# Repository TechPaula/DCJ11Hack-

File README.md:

# DCJ11Hack+
DCJ11 Hack+ related boards, PAL code and example code
by Paula Maddox http://maddoxp.pro

This is my first github project, I've decided to share my DCJ11 based board. It's based heavily on the word done by Beent Hilpert http://madrona.ca/e/pdp11hack/ but I wanted to able to add and remove functionality via a back plane.

I've long admired this chip for no other reason than it looks so freekin' cool, I mean just look at it, it's gorgeous.

## The Boards
So far There is the main CPU board and also the RAM, ROM and text display board. You'll find the schematics and PCB files here and they were made in KiCAD. I've also included the PAL files for each of the PALs on the board (one on each board). Hopefully this will give you enough to get going.
The text displays are mounted on the opposite side to the RAM/ROM chips as I wanted to be able to see the text and also be able to turn it to see the DCJ11 chip (did I say how gorgeous this chip is?).

Now there's a 16x16 Dot Matrix display, it does have two levels of brightness (just two overlapping portions of 32 bytes of RAM), but the difference between dim and bright isn't very much.

I got my backplane from eBay here - https://www.ebay.co.uk/itm/284367015211 and the same seller also does backplanes with more slots.

When it powers up the chip jumps to it's "ODT" mode rather than running code, this was done to allow me to play around with thinngs and get an understanding of the chip. 
The default baud rate is 115200 and uses 8bits, 1 stop and no  parity. 

## Memory Map
My memory map is as follows and was updated on 07/04/2024;

### HEX
* 0x0000 - 0x7FFE = RAM  (32K)
* 0x6000 - 0x7FFE = Text Display (shadowed in RAM as it's WRITE only)
* 0x8000 - 0xBFFE = ROM  (16K)
* 0xC000 - 0xDFFE = Matrix display
* 0xE000 - 0xFFFE = Future

### OCTAL (has to end on a multiple of 2)
* 000 000 - 077 776 - RAM
* 060 000 - 060 020 - Text Display (repeated multiple times)
* 100 000 - 137 776 - ROM
* 140 000 - 157 776 - Matrix Display
* 160 000 - 177 776 - Future

## Code examples
The code examples are for a basic "Hello World!" which just writes characters to the display memory, there's also a more intelligent one. I've also included a "Knight Rider" (or Cylon if you prefer) bit of code and finally a terminal test code which spits "B" to the console (hit the halt switch to stop it).

You'll find the .asm files and the .oct files.

I use the pdp11 simulator found here https://programmer209.wordpress.com/2011/08/14/pdp-11-assembly-language-simulator/ to compile and test my code, there are others but this is a lot easier to copy and paste code into :)

There is also a pretty good guide to the PDP11 instruction set here - https://programmer209.wordpress.com/2011/08/03/the-pdp-11-assembly-language/

of note, this board **ONLY** supports 16bit wide read/writes, i.e. "word" only, if you use byte commands it will destroy one half of the memory, in the same way as the PDP11 Hack board does, this is less than ideal but it simplifies the circuitry needed a lot.

I user TeraTerm to upload the code, I use a 10mS character and line feed delay, just to give the CPU a chance to respond when it sees the "/".

## The future

Finally, I do this for a hobby and for fun, so I don't know when I will add more code or do the third board.

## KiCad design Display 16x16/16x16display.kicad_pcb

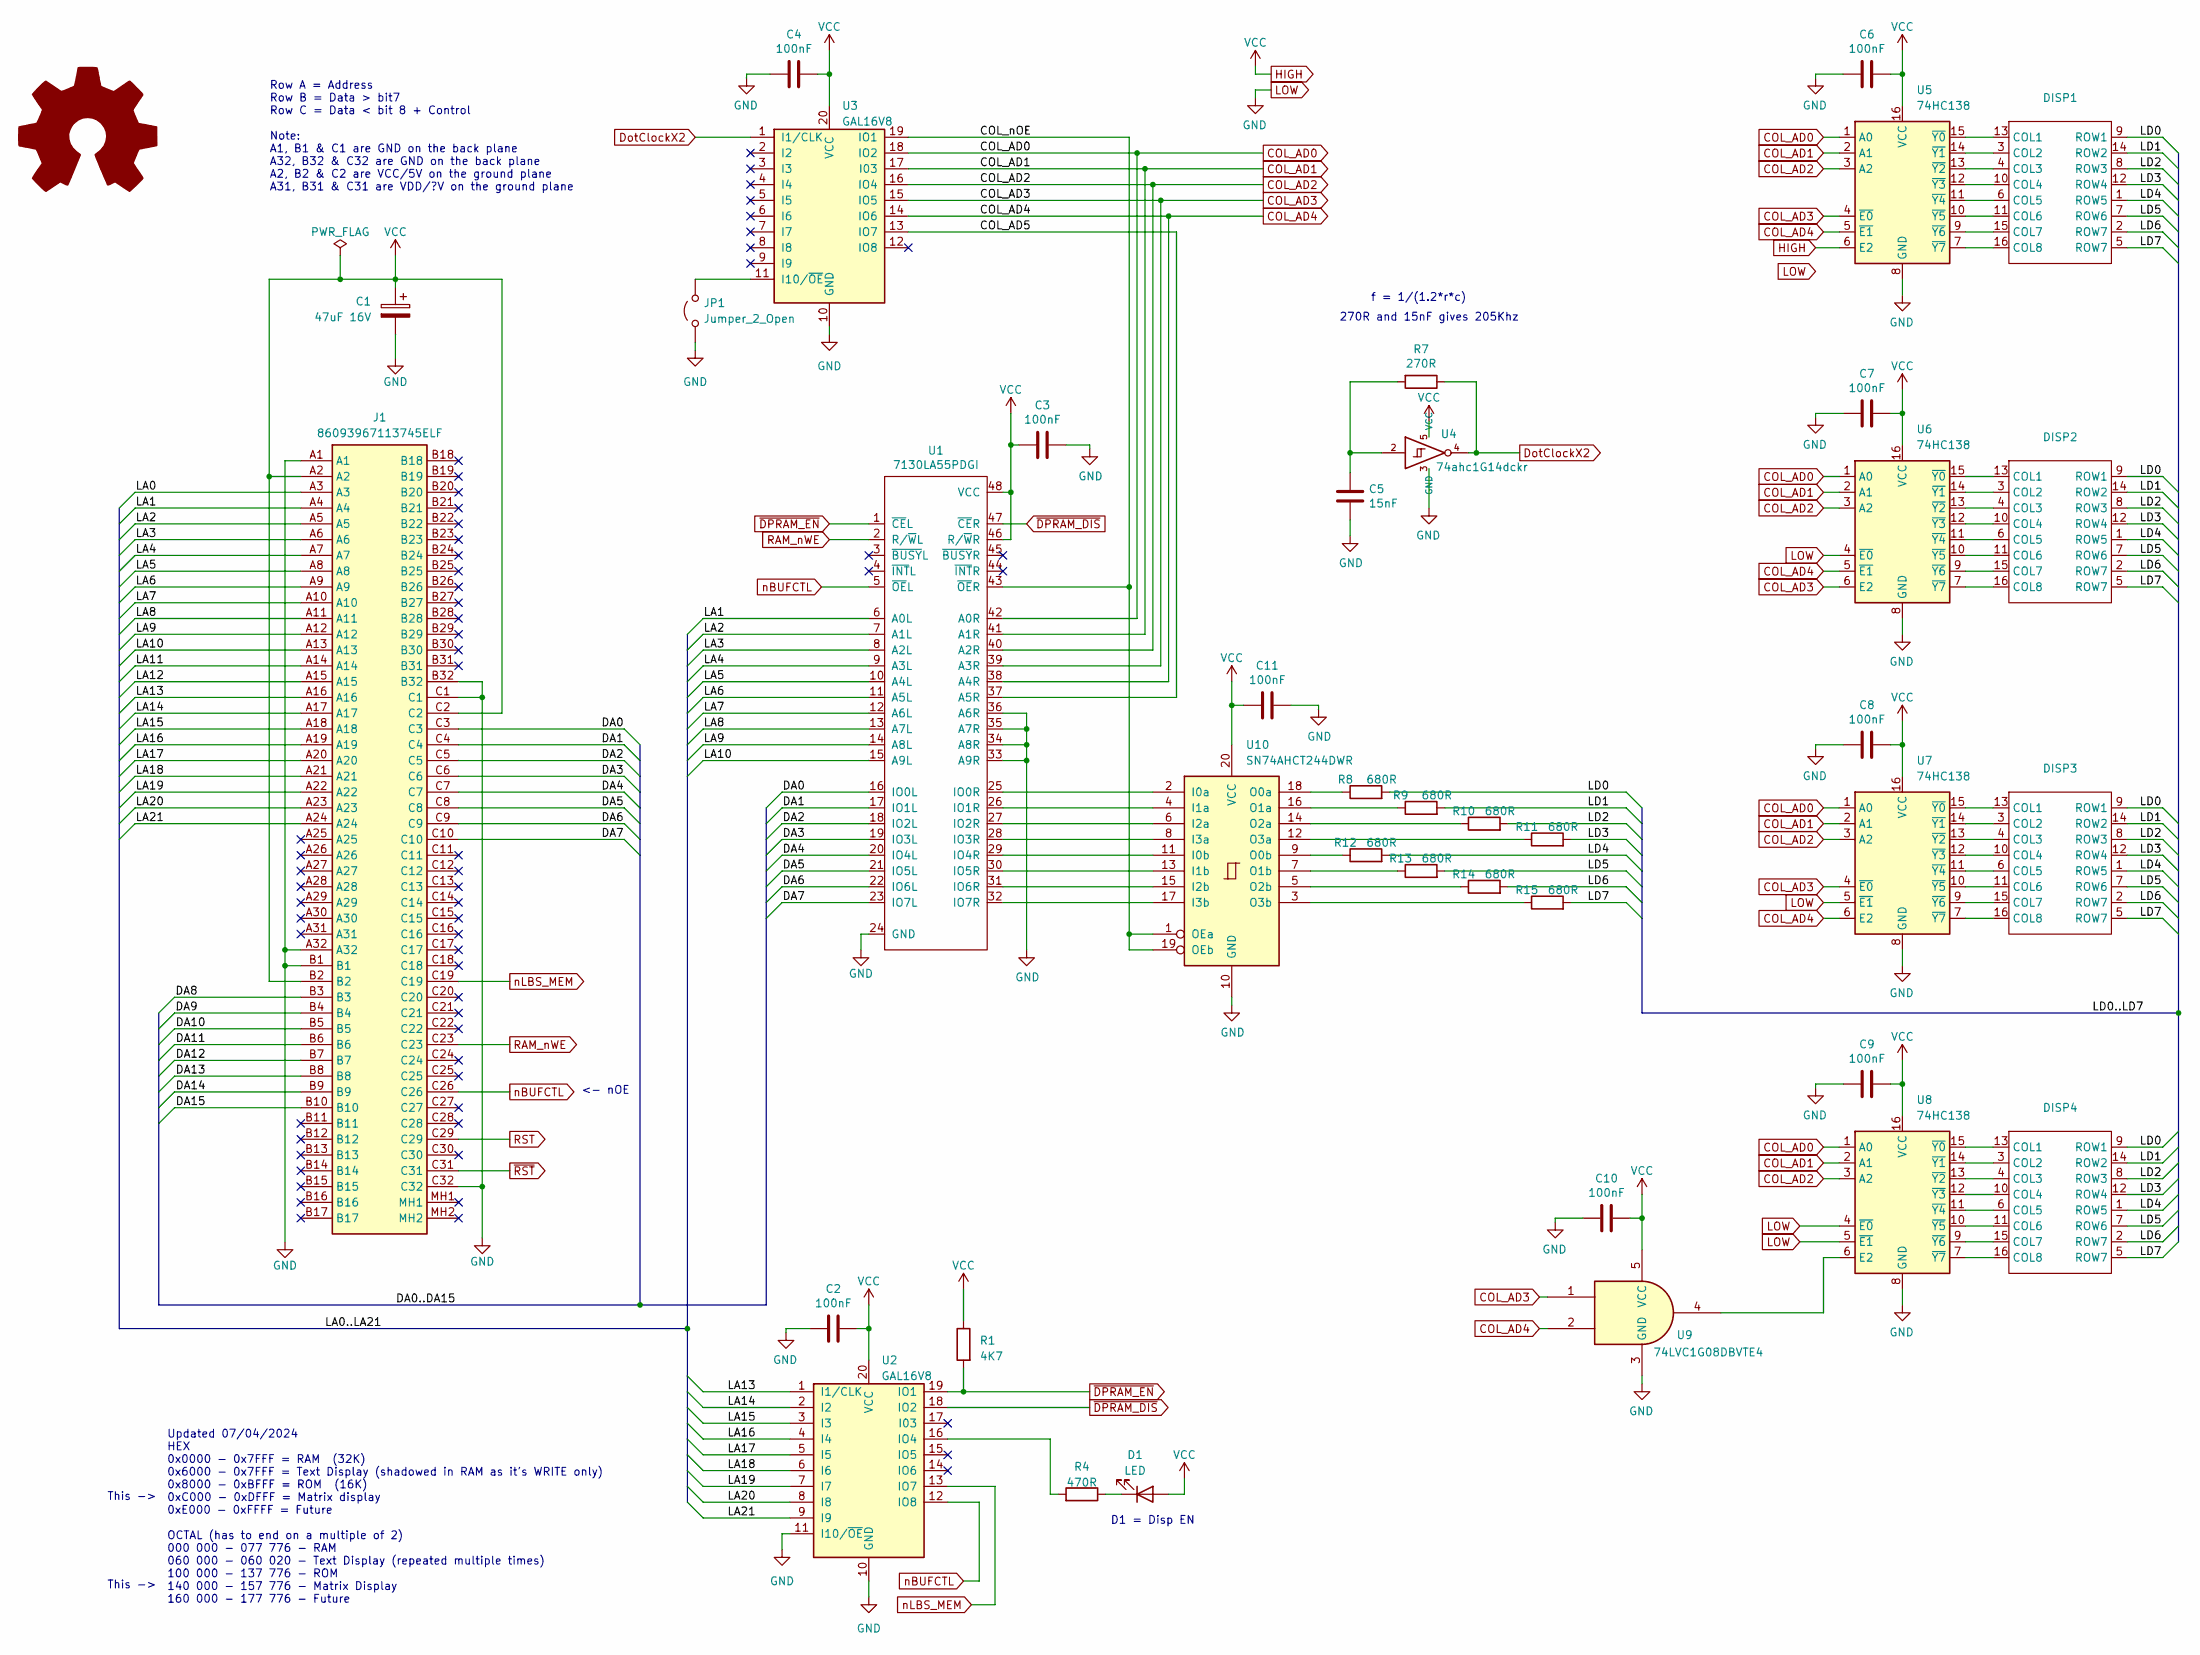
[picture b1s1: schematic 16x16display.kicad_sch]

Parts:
C1: 47uF 16V; CP_Elec_6.3x5.8
C2, C3, C4, C6, C7, C8, C9, C10, C11: 100nF; C_0603_1608Metric; LCSC C14663
C5: 15nF; C_0603_1608Metric; LCSC C1596
D1: LED; LTL4221NHBP
DISP1, DISP2, DISP3, DISP4: 788AS
J1: 86093967113745ELF; Manufacturer_Part_Number 86093967113745ELF
JP1: Jumper_2_Open; SolderJumper-2_P1.3mm_Open_TrianglePad1.0x1.5mm
R1: 4K7; R_0603_1608Metric_Pad0.98x0.95mm_HandSolder
R4: 470R; R_0603_1608Metric_Pad0.98x0.95mm_HandSolder
R7: 270R; R_0603_1608Metric; LCSC C22966
R8, R9, R10, R11, R12, R13, R14, R15: 680R; R_0603_1608Metric_Pad0.98x0.95mm_HandSolder
SYM1: Logo_Open_Hardware_Large; Fox_avatar_18mm
U1: 7130LA55PDGI; DIP-48_W15.24mm_Socket
U2, U3: GAL16V8; DIP-20_W7.62mm
U4: 74ahc1G14dckr; SOT-353_SC-70-5; Mouser Part Number 595-SN74AHC1G14DCKR; LCSC C66196
U5, U6, U7, U8: 74HC138; SO-16_3.9x9.9mm_P1.27mm
U9: 74LVC1G08DBVTE4; SOT-23-5_HandSoldering; Mouser Part Number 595-74LVC1G08DBVTE4
U10: SN74AHCT244DWR; SOIC-20W_7.5x12.8mm_P1.27mm

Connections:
/COL_AD5: U1.37 (A5R), U3.13 (IO7)
/COL_nOE: U1.43 (~OER), U3.19 (IO1), U10.1 (OEa), U10.19 (OEb)
/DA0: J1.C3, U1.16 (IO0L)
/DA1: J1.C4, U1.17 (IO1L)
/DA2: J1.C5, U1.18 (IO2L)
/DA3: J1.C6, U1.19 (IO3L)
/DA4: J1.C7, U1.20 (IO4L)
/DA5: J1.C8, U1.21 (IO5L)
/DA6: J1.C9, U1.22 (IO6L)
/DA7: J1.C10, U1.23 (IO7L)
/DA8: J1.B3
/DA9: J1.B4
/DA10: J1.B5
/DA11: J1.B6
/DA12: J1.B7
/DA13: J1.B8
/DA14: J1.B9
/DA15: J1.B10
/LA0: J1.A3
/LA1: J1.A4, U1.6 (A0L)
/LA2: J1.A5, U1.7 (A1L)
/LA3: J1.A6, U1.8 (A2L)
/LA4: J1.A7, U1.9 (A3L)
/LA5: J1.A8, U1.10 (A4L)
/LA6: J1.A9, U1.11 (A5L)
/LA7: J1.A10, U1.12 (A6L)
/LA8: J1.A11, U1.13 (A7L)
/LA9: J1.A12, U1.14 (A8L)
/LA10: J1.A13, U1.15 (A9L)
/LA11: J1.A14
/LA12: J1.A15
/LA13: J1.A16, U2.1 (I1/CLK)
/LA14: J1.A17, U2.2 (I2)
/LA15: J1.A18, U2.3 (I3)
/LA16: J1.A19, U2.4 (I4)
/LA17: J1.A20, U2.5 (I5)
/LA18: J1.A21, U2.6 (I6)
/LA19: J1.A22, U2.7 (I7)
/LA20: J1.A23, U2.8 (I8)
/LA21: J1.A24, U2.9 (I9)
/LD0: DISP1.9 (ROW1), DISP2.9 (ROW1), DISP3.9 (ROW1), DISP4.9 (ROW1), R8.2
/LD1: DISP1.14 (ROW2), DISP2.14 (ROW2), DISP3.14 (ROW2), DISP4.14 (ROW2), R9.2
/LD2: DISP1.8 (ROW3), DISP2.8 (ROW3), DISP3.8 (ROW3), DISP4.8 (ROW3), R10.2
/LD3: DISP1.12 (ROW4), DISP2.12 (ROW4), DISP3.12 (ROW4), DISP4.12 (ROW4), R11.2
/LD4: DISP1.1 (ROW5), DISP2.1 (ROW5), DISP3.1 (ROW5), DISP4.1 (ROW5), R12.2
/LD5: DISP1.7 (ROW6), DISP2.7 (ROW6), DISP3.7 (ROW6), DISP4.7 (ROW6), R13.2
/LD6: DISP1.2 (ROW7), DISP2.2 (ROW7), DISP3.2 (ROW7), DISP4.2 (ROW7), R14.2
/LD7: DISP1.5 (ROW7), DISP2.5 (ROW7), DISP3.5 (ROW7), DISP4.5 (ROW7), R15.2
COL_AD0: U1.42 (A0R), U3.18 (IO2), U5.1 (A0), U6.1 (A0), U7.1 (A0), U8.1 (A0)
COL_AD1: U1.41 (A1R), U3.17 (I03), U5.2 (A1), U6.2 (A1), U7.2 (A1), U8.2 (A1)
COL_AD2: U1.40 (A2R), U3.16 (IO4), U5.3 (A2), U6.3 (A2), U7.3 (A2), U8.3 (A2)
COL_AD3: U1.39 (A3R), U3.15 (IO5), U5.4 (~E0), U6.6 (E2), U7.4 (~E0), U9.1
COL_AD4: U1.38 (A4R), U3.14 (IO6), U5.5 (~E1), U6.5 (~E1), U7.6 (E2), U9.2
DotClockX2: R7.1, U3.1 (I1/CLK), U4.4
HIGH: C1.1, C2.2, C3.2, C4.2, C6.2, C7.2, C8.2, C9.2, C10.2, C11.2, D1.2 (A), J1.A2, J1.B2, J1.C2, R1.1, U1.46 (R/~WR), U1.48 (VCC), U2.20 (VCC), U3.20 (VCC), U4.5 (VCC), U5.6 (E2), U5.16 (VCC), U6.16 (VCC), U7.16 (VCC), U8.16 (VCC), U9.5 (VCC), U10.20 (VCC)
LOW: C1.2, C2.1, C3.1, C4.1, C5.2, C6.1, C7.1, C8.1, C9.1, C10.1, C11.1, J1.A1, J1.A32, J1.B1, J1.B32, J1.C1, J1.C32, JP1.1 (A), U1.24 (GND), U1.33 (A9R), U1.34 (A8R), U1.35 (A7R), U1.36 (A6R), U2.10 (GND), U2.11 (I10/~OE), U3.10 (GND), U4.3 (GND), U5.8 (GND), U6.4 (~E0), U6.8 (GND), U7.5 (~E1), U7.8 (GND), U8.4 (~E0), U8.5 (~E1), U8.8 (GND), U9.3 (GND), U10.10 (GND)
unnamed: C5.1, R7.2, U4.2
unnamed: D1.1 (K), R4.1
unnamed: DISP1.13 (COL1), U5.15 (~Y0)
unnamed: DISP1.3 (COL2), U5.14 (~Y1)
unnamed: DISP1.4 (COL3), U5.13 (~Y2)
unnamed: DISP1.10 (COL4), U5.12 (~Y3)
unnamed: DISP1.6 (COL5), U5.11 (~Y4)
unnamed: DISP1.11 (COL6), U5.10 (~Y5)
unnamed: DISP1.15 (COL7), U5.9 (~Y6)
unnamed: DISP1.16 (COL8), U5.7 (~Y7)
unnamed: DISP2.13 (COL1), U6.15 (~Y0)
unnamed: DISP2.3 (COL2), U6.14 (~Y1)
unnamed: DISP2.4 (COL3), U6.13 (~Y2)
unnamed: DISP2.10 (COL4), U6.12 (~Y3)
unnamed: DISP2.6 (COL5), U6.11 (~Y4)
unnamed: DISP2.11 (COL6), U6.10 (~Y5)
unnamed: DISP2.15 (COL7), U6.9 (~Y6)
unnamed: DISP2.16 (COL8), U6.7 (~Y7)
unnamed: DISP3.13 (COL1), U7.15 (~Y0)
unnamed: DISP3.3 (COL2), U7.14 (~Y1)
unnamed: DISP3.4 (COL3), U7.13 (~Y2)
unnamed: DISP3.10 (COL4), U7.12 (~Y3)
unnamed: DISP3.6 (COL5), U7.11 (~Y4)
unnamed: DISP3.11 (COL6), U7.10 (~Y5)
unnamed: DISP3.15 (COL7), U7.9 (~Y6)
unnamed: DISP3.16 (COL8), U7.7 (~Y7)
unnamed: DISP4.13 (COL1), U8.15 (~Y0)
unnamed: DISP4.3 (COL2), U8.14 (~Y1)
unnamed: DISP4.4 (COL3), U8.13 (~Y2)
unnamed: DISP4.10 (COL4), U8.12 (~Y3)
unnamed: DISP4.6 (COL5), U8.11 (~Y4)
unnamed: DISP4.11 (COL6), U8.10 (~Y5)
unnamed: DISP4.15 (COL7), U8.9 (~Y6)
unnamed: DISP4.16 (COL8), U8.7 (~Y7)
unnamed: JP1.2 (B), U3.11 (I10/~OE)
unnamed: U1.25 (IO0R), U10.2 (I0a)
unnamed: U1.26 (IO1R), U10.4 (I1a)
unnamed: U1.27 (IO2R), U10.6 (I2a)
unnamed: U1.28 (IO3R), U10.8 (I3a)
unnamed: U1.29 (IO4R), U10.11 (I0b)
unnamed: U1.30 (IO5R), U10.13 (I1b)
unnamed: U1.31 (IO6R), U10.15 (I2b)
unnamed: U1.32 (IO7R), U10.17 (I3b)
unnamed: R4.2, U2.16 (IO4)
unnamed: U8.6 (E2), U9.4
unnamed: R8.1, U10.18 (O0a)
unnamed: R12.1, U10.9 (O0b)
unnamed: R9.1, U10.16 (O1a)
unnamed: R13.1, U10.7 (O1b)
unnamed: R10.1, U10.14 (O2a)
unnamed: R14.1, U10.5 (O2b)
unnamed: R11.1, U10.12 (O3a)
unnamed: R15.1, U10.3 (O3b)
RAM_nWE: J1.C23, U1.2 (R/~WL)
RST: J1.C29
nBUFCTL: J1.C26, U1.5 (~OEL), U2.12 (IO8)
nLBS_MEM: J1.C19, U2.13 (IO7)
~DPRAM_DIS: U1.47 (~CER), U2.18 (IO2)
~DPRAM_EN: R1.2, U1.1 (~CEL), U2.19 (IO1)
~RST: J1.C31

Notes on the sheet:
<- nOE
Row A = Address Row B = Data > bit7 Row C = Data < bit 8 + Control Note: A1, B1 & C1 are GND on the back plane A32, B32 & C32 are GND on the back plane A2, B2 & C2 are VCC/5V on the ground plane A31, B31 & C31 are VDD/?V on the ground plane
This ->
270R and 15nF gives 205Khz
Updated 07/04/2024 HEX 0x0000 - 0x7FFF = RAM (32K) 0x6000 - 0x7FFF = Text Display (shadowed in RAM as it's WRITE only) 0x8000 - 0xBFFF = ROM (16K) 0xC000 - 0xDFFF = Matrix display 0xE000 - 0xFFFF = Future OCTAL (has to end on a multiple of 2) 000 000 - 077 776 - RAM 060 000 - 060 020 - Text Display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
D1 = Disp EN
f = 1/(1.2*r*c)

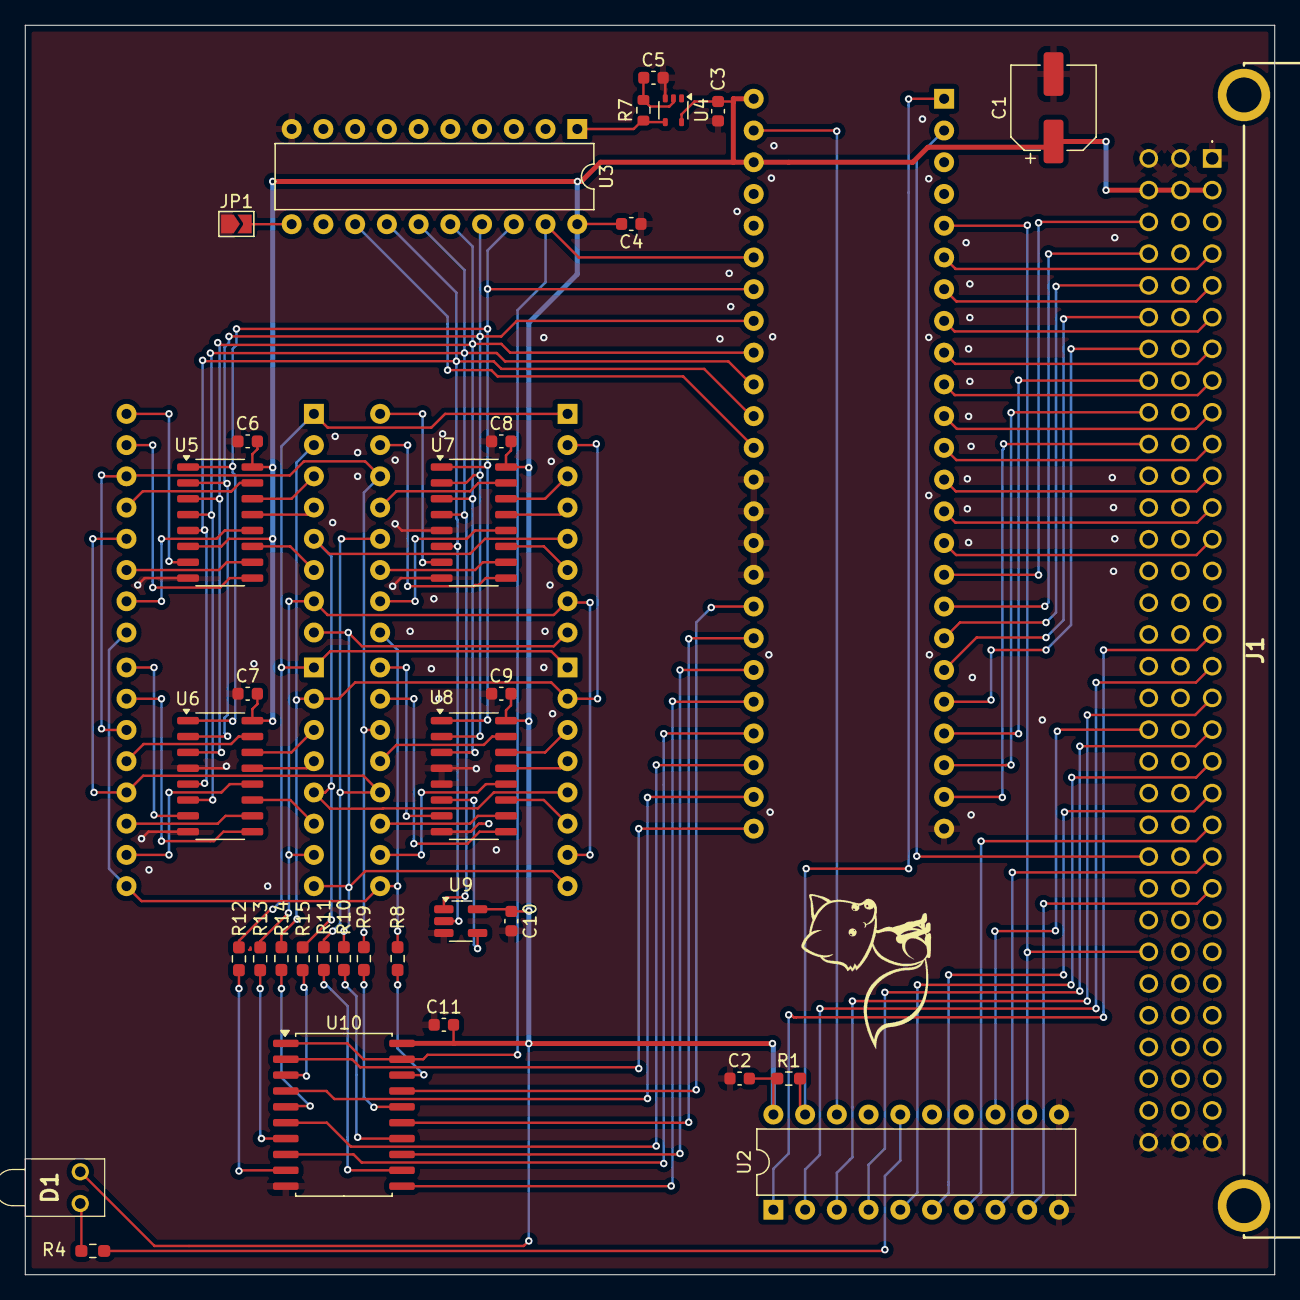
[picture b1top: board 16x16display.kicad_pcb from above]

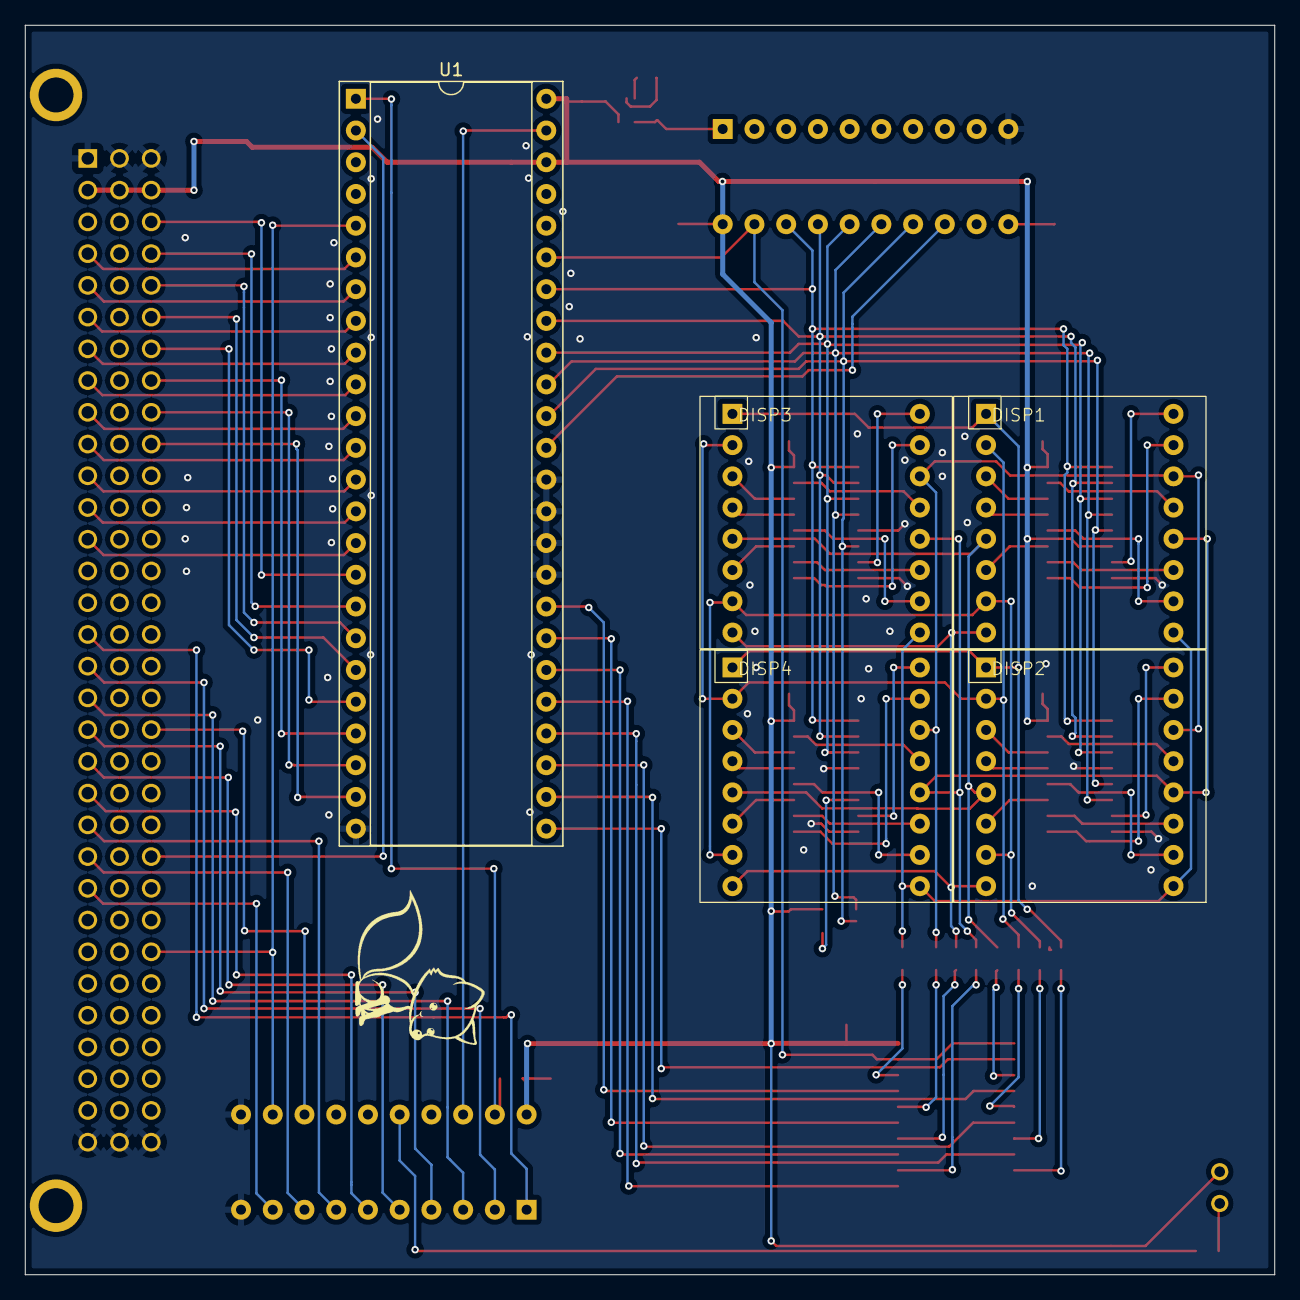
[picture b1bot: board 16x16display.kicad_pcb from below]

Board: 2 copper layers, 100.0 x 100.0 mm, 41 parts (6 on the bottom side), 103 nets.

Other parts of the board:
SYM1#2: Logo_Open_Hardware_Large; Fox_avatar_18mm

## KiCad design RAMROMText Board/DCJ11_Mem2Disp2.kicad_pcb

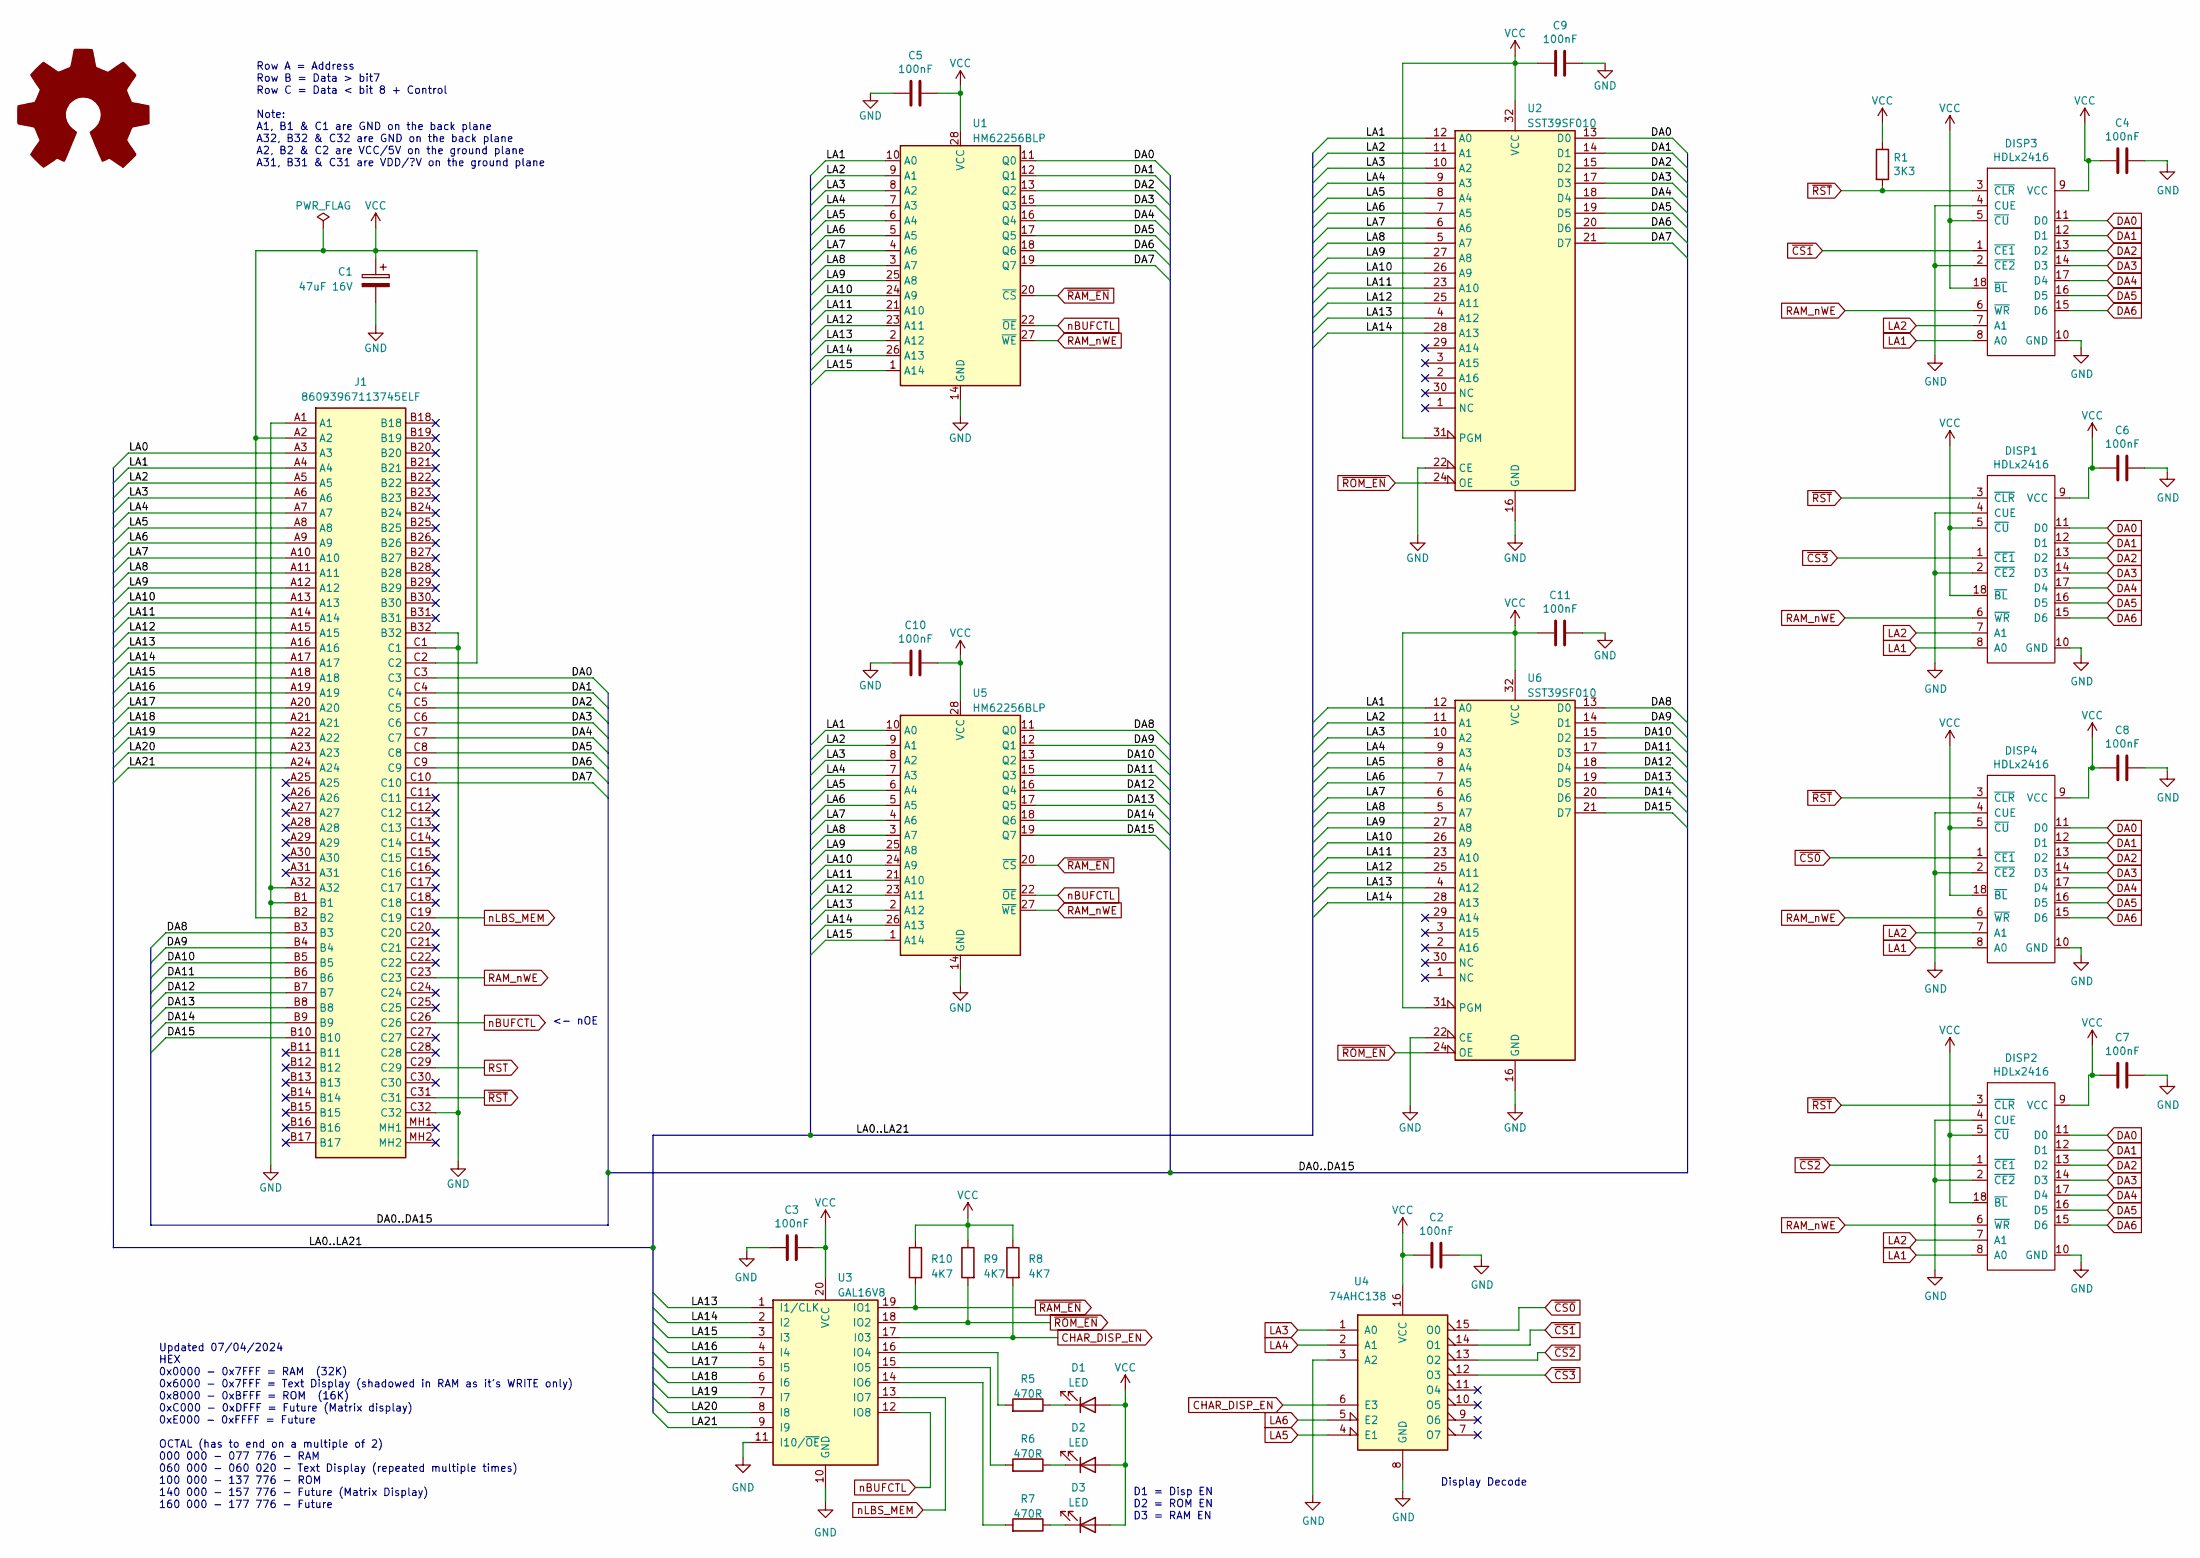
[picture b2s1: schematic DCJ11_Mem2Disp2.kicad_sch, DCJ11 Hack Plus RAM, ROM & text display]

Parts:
C1: 47uF 16V; CP_Elec_6.3x5.8
C2, C3, C4, C5, C6, C7, C8, C9, C10, C11: 100nF; C_0603_1608Metric; LCSC C14663
D1, D2, D3: LED; LTL4221NHBP
DISP1, DISP2, DISP3, DISP4: HDLx2416; LCSC DNP
J1: 86093967113745ELF; Manufacturer_Part_Number 86093967113745ELF
R1: 3K3; R_0603_1608Metric; LCSC C22978
R5, R6, R7: 470R; R_0603_1608Metric_Pad0.98x0.95mm_HandSolder
R8, R9, R10: 4K7; R_0603_1608Metric_Pad0.98x0.95mm_HandSolder
SYM1: Logo_Open_Hardware_Large; Fox_avatar_18mm
U1, U5: HM62256BLP; DIP-28_W15.24mm
U2, U6: SST39SF010; DIP-32_W15.24mm
U3: GAL16V8; DIP-20_W7.62mm
U4: 74AHC138; SOIC-16_3.9x9.9mm_P1.27mm; LCSC C132055

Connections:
/DA7: J1.C10, U1.19 (Q7), U2.21 (D7)
/DA8: J1.B3, U5.11 (Q0), U6.13 (D0)
/DA9: J1.B4, U5.12 (Q1), U6.14 (D1)
/DA10: J1.B5, U5.13 (Q2), U6.15 (D2)
/DA11: J1.B6, U5.15 (Q3), U6.17 (D3)
/DA12: J1.B7, U5.16 (Q4), U6.18 (D4)
/DA13: J1.B8, U5.17 (Q5), U6.19 (D5)
/DA14: J1.B9, U5.18 (Q6), U6.20 (D6)
/DA15: J1.B10, U5.19 (Q7), U6.21 (D7)
/LA0: J1.A3
/LA7: J1.A10, U1.4 (A6), U2.6 (A6), U5.4 (A6), U6.6 (A6)
/LA8: J1.A11, U1.3 (A7), U2.5 (A7), U5.3 (A7), U6.5 (A7)
/LA9: J1.A12, U1.25 (A8), U2.27 (A8), U5.25 (A8), U6.27 (A8)
/LA10: J1.A13, U1.24 (A9), U2.26 (A9), U5.24 (A9), U6.26 (A9)
/LA11: J1.A14, U1.21 (A10), U2.23 (A10), U5.21 (A10), U6.23 (A10)
/LA12: J1.A15, U1.23 (A11), U2.25 (A11), U5.23 (A11), U6.25 (A11)
/LA13: J1.A16, U1.2 (A12), U2.4 (A12), U3.1 (I1/CLK), U5.2 (A12), U6.4 (A12)
/LA14: J1.A17, U1.26 (A13), U2.28 (A13), U3.2 (I2), U5.26 (A13), U6.28 (A13)
/LA15: J1.A18, U1.1 (A14), U3.3 (I3), U5.1 (A14)
/LA16: J1.A19, U3.4 (I4)
/LA17: J1.A20, U3.5 (I5)
/LA18: J1.A21, U3.6 (I6)
/LA19: J1.A22, U3.7 (I7)
/LA20: J1.A23, U3.8 (I8)
/LA21: J1.A24, U3.9 (I9)
CHAR_DISP_EN: R8.2, U3.17 (I03), U4.6 (E3)
DA0: DISP1.11 (D0), DISP2.11 (D0), DISP3.11 (D0), DISP4.11 (D0), J1.C3, U1.11 (Q0), U2.13 (D0)
DA1: DISP1.12 (D1), DISP2.12 (D1), DISP3.12 (D1), DISP4.12 (D1), J1.C4, U1.12 (Q1), U2.14 (D1)
DA2: DISP1.13 (D2), DISP2.13 (D2), DISP3.13 (D2), DISP4.13 (D2), J1.C5, U1.13 (Q2), U2.15 (D2)
DA3: DISP1.14 (D3), DISP2.14 (D3), DISP3.14 (D3), DISP4.14 (D3), J1.C6, U1.15 (Q3), U2.17 (D3)
DA4: DISP1.17 (D4), DISP2.17 (D4), DISP3.17 (D4), DISP4.17 (D4), J1.C7, U1.16 (Q4), U2.18 (D4)
DA5: DISP1.16 (D5), DISP2.16 (D5), DISP3.16 (D5), DISP4.16 (D5), J1.C8, U1.17 (Q5), U2.19 (D5)
DA6: DISP1.15 (D6), DISP2.15 (D6), DISP3.15 (D6), DISP4.15 (D6), J1.C9, U1.18 (Q6), U2.20 (D6)
GND: C1.2, C2.1, C3.1, C4.1, C5.2, C6.1, C7.1, C8.1, C9.2, C10.2, C11.2, DISP1.2 (~CE2), DISP1.4 (CUE), DISP1.10 (GND), DISP2.2 (~CE2), DISP2.4 (CUE), DISP2.10 (GND), DISP3.2 (~CE2), DISP3.4 (CUE), DISP3.10 (GND), DISP4.2 (~CE2), DISP4.4 (CUE), DISP4.10 (GND), J1.A1, J1.A32, J1.B1, J1.B32, J1.C1, J1.C32, U1.14 (GND), U2.16 (GND), U2.22 (CE), U3.10 (GND), U3.11 (I10/~OE), U4.3 (A2), U4.8 (GND), U5.14 (GND), U6.16 (GND), U6.22 (CE)
LA1: DISP1.8 (A0), DISP2.8 (A0), DISP3.8 (A0), DISP4.8 (A0), J1.A4, U1.10 (A0), U2.12 (A0), U5.10 (A0), U6.12 (A0)
LA2: DISP1.7 (A1), DISP2.7 (A1), DISP3.7 (A1), DISP4.7 (A1), J1.A5, U1.9 (A1), U2.11 (A1), U5.9 (A1), U6.11 (A1)
LA3: J1.A6, U1.8 (A2), U2.10 (A2), U4.1 (A0), U5.8 (A2), U6.10 (A2)
LA4: J1.A7, U1.7 (A3), U2.9 (A3), U4.2 (A1), U5.7 (A3), U6.9 (A3)
LA5: J1.A8, U1.6 (A4), U2.8 (A4), U4.4 (E1), U5.6 (A4), U6.8 (A4)
LA6: J1.A9, U1.5 (A5), U2.7 (A5), U4.5 (E2), U5.5 (A5), U6.7 (A5)
unnamed: D1.1 (K), R5.1
unnamed: D2.1 (K), R6.1
unnamed: D3.1 (K), R7.1
unnamed: R5.2, U3.16 (IO4)
unnamed: R6.2, U3.15 (IO5)
unnamed: R7.2, U3.14 (IO6)
RAM_nWE: DISP1.6 (~WR), DISP2.6 (~WR), DISP3.6 (~WR), DISP4.6 (~WR), J1.C23, U1.27 (~WE), U5.27 (~WE)
RST: J1.C29
VCC: C1.1, C2.2, C3.2, C4.2, C5.1, C6.2, C7.2, C8.2, C9.1, C10.1, C11.1, D1.2 (A), D2.2 (A), D3.2 (A), DISP1.5 (~CU), DISP1.9 (VCC), DISP1.18 (~BL), DISP2.5 (~CU), DISP2.9 (VCC), DISP2.18 (~BL), DISP3.5 (~CU), DISP3.9 (VCC), DISP3.18 (~BL), DISP4.5 (~CU), DISP4.9 (VCC), DISP4.18 (~BL), J1.A2, J1.B2, J1.C2, R1.1, R8.1, R9.1, R10.1, U1.28 (VCC), U2.31 (PGM), U2.32 (VCC), U3.20 (VCC), U4.16 (VCC), U5.28 (VCC), U6.31 (PGM), U6.32 (VCC)
nBUFCTL: J1.C26, U1.22 (~OE), U3.12 (IO8), U5.22 (~OE)
nLBS_MEM: J1.C19, U3.13 (IO7)
~CS0: DISP4.1 (~CE1), U4.15 (O0)
~CS1: DISP3.1 (~CE1), U4.14 (O1)
~CS2: DISP2.1 (~CE1), U4.13 (O2)
~CS3: DISP1.1 (~CE1), U4.12 (O3)
~RAM_EN: R10.2, U1.20 (~CS), U3.19 (IO1), U5.20 (~CS)
~ROM_EN: R9.2, U2.24 (OE), U3.18 (IO2), U6.24 (OE)
~RST: DISP1.3 (~CLR), DISP2.3 (~CLR), DISP3.3 (~CLR), DISP4.3 (~CLR), J1.C31, R1.2

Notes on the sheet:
Updated 07/04/2024 HEX 0x0000 - 0x7FFF = RAM (32K) 0x6000 - 0x7FFF = Text Display (shadowed in RAM as it's WRITE only) 0x8000 - 0xBFFF = ROM (16K) 0xC000 - 0xDFFF = Future (Matrix display) 0xE000 - 0xFFFF = Future OCTAL (has to end on a multiple of 2) 000 000 - 077 776 - RAM 060 000 - 060 020 - Tex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
Display Decode
Row A = Address Row B = Data > bit7 Row C = Data < bit 8 + Control Note: A1, B1 & C1 are GND on the back plane A32, B32 & C32 are GND on the back plane A2, B2 & C2 are VCC/5V on the ground plane A31, B31 & C31 are VDD/?V on the ground plane
D1 = Disp EN D2 = ROM EN D3 = RAM EN
<- nOE

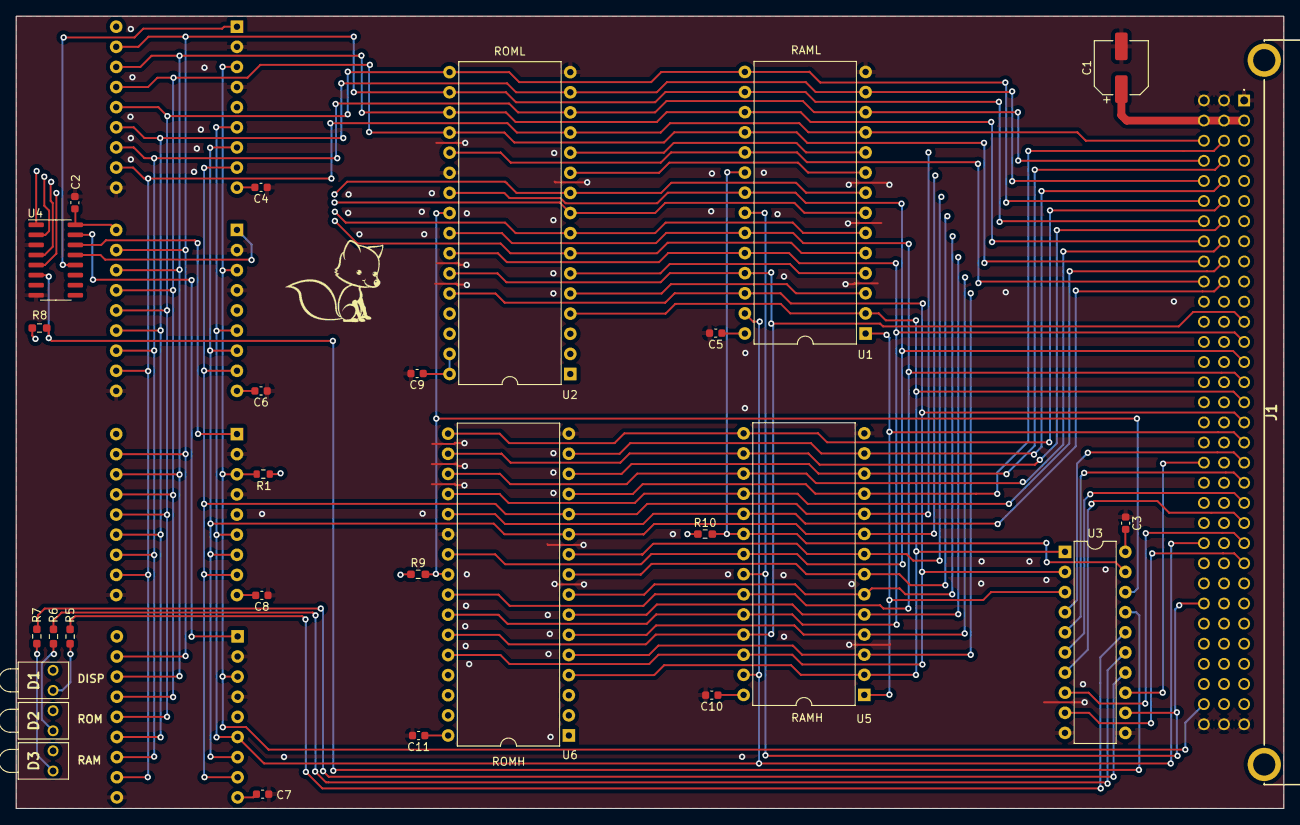
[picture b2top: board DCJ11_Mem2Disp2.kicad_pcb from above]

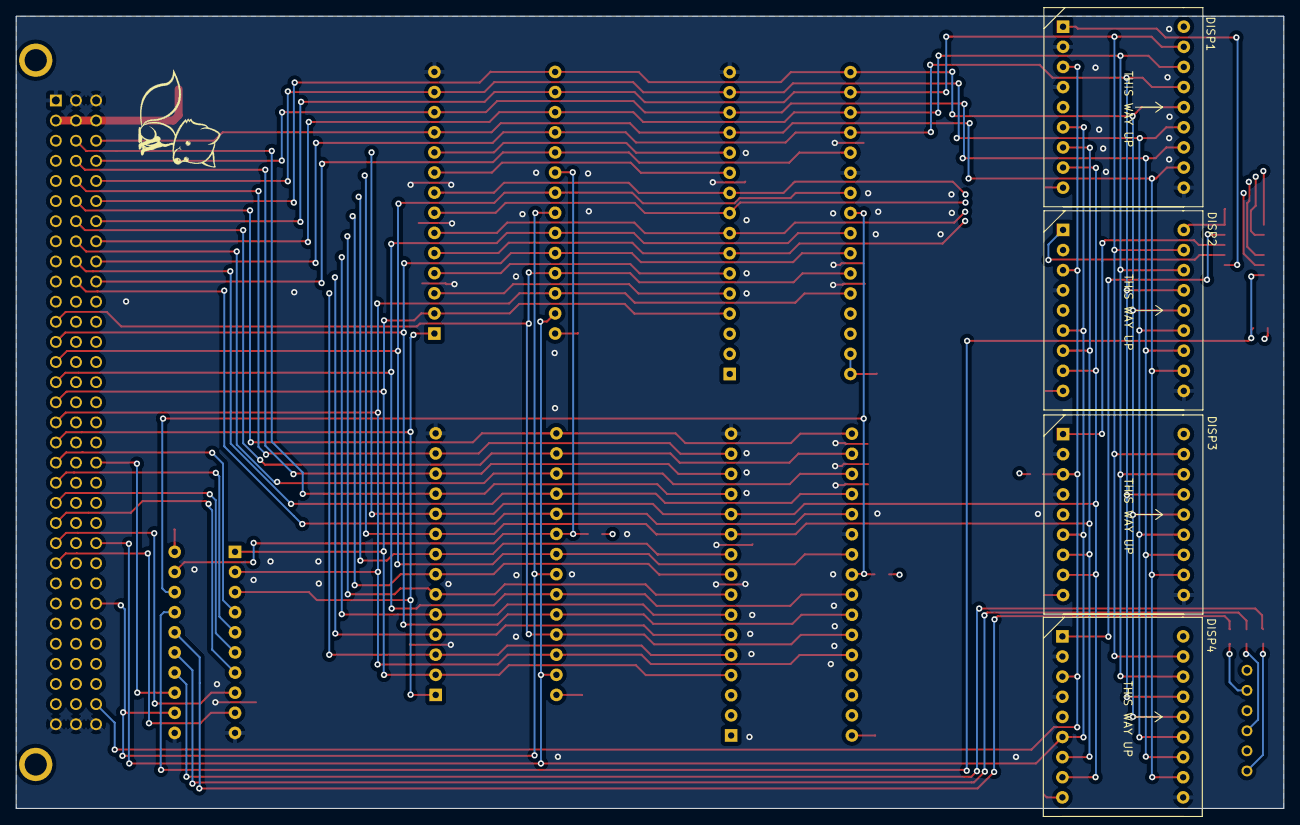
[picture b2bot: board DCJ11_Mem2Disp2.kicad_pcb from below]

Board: 4 copper layers, 160.0 x 100.0 mm, 34 parts (5 on the bottom side), 56 nets.

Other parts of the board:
SYM1#2: Logo_Open_Hardware_Large; Fox_avatar_18mm
